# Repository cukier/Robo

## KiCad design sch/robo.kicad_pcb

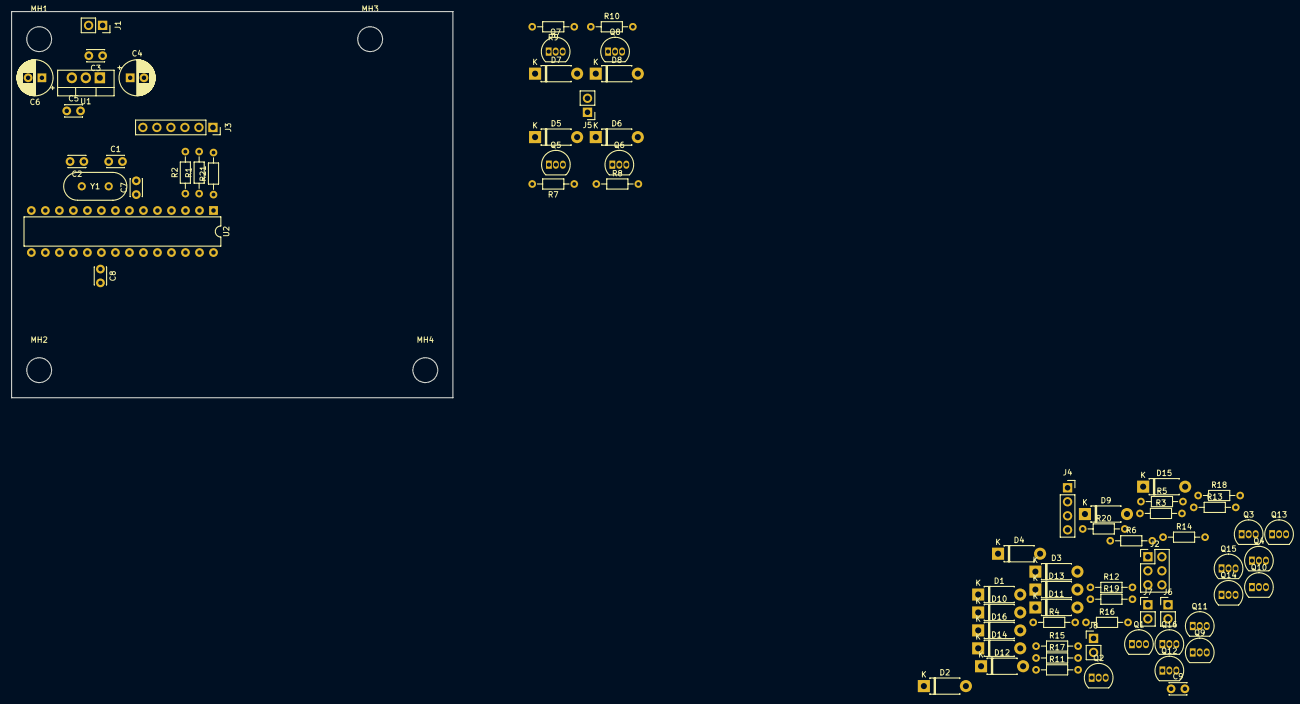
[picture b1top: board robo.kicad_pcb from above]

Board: 2 copper layers, 80.0 x 70.0 mm, 77 parts (0 on the bottom side), 47 nets, no tracks yet.

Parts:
C1, C2: 22nF; C_Disc_D3.0mm_W2.0mm_P2.50mm
C3, C5, C7, C8, C9: 100nF; C_Disc_D3.0mm_W2.0mm_P2.50mm
C4, C6: 470uF; CP_Radial_D6.3mm_P2.50mm
D1, D2, D3, D4, D5, D6, D7, D8, D9, D10, D11, D12, D13, D14, D15, D16: D; D_DO-41_SOD81_P7.62mm_Horizontal
J1: PWR; PinSocket_1x02_P2.54mm_Vertical
J2: ICSP; PinHeader_2x03_P2.54mm_Vertical
J3: Serial; PinSocket_1x06_P2.54mm_Vertical
J4: HC-04; PinSocket_1x04_P2.54mm_Vertical
J5: MOTOR 1; PinHeader_1x02_P2.54mm_Vertical
J6: MOTOR 4; PinHeader_1x02_P2.54mm_Vertical
J7: MOTOR 3; PinHeader_1x02_P2.54mm_Vertical
J8: MOTOR 2; PinHeader_1x02_P2.54mm_Vertical
MH1, MH2, MH3, MH4: MountingHole; MountingHole_4.5mm
Q1, Q2, Q3, Q4, Q5, Q6, Q7, Q8, Q9, Q10, Q11, Q12, Q13, Q14, Q15, Q16: BC337; TO-92_Inline
R1, R2, R3, R4, R5, R6, R7, R8, R9, R10, R11, R12, R13, R14, R15, R16, R17, R18, R19, R20, R21: 1k; R_Axial_DIN0204_L3.6mm_D1.6mm_P7.62mm_Horizontal
U1: L7805; TO-220-3_Vertical
U2: ATmega328P-PU; DIP-28_W7.62mm
Y1: Crystal; Crystal_HC49-4H_Vertical

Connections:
+5V: C5.1, C6.1, C7.1, C8.1, C9.1, D1.1, D3.1, D5.1, D7.1, D9.1, D11.1, D13.1, D15.1, J2.6, J4.1, Q1.1, Q3.1, Q5.1, Q7.1, Q9.1, Q11.1, Q13.1, Q15.1, R21.2, U1.3, U2.7, U2.20
/BRIDGE_H1: R7.2, R10.2, U2.4
/BRIDGE_H2: R17.2, R20.2, U2.5
/BRIDGE_H3: R3.2, R6.2, U2.6
/BRIDGE_H4: R13.2, R16.2, U2.11
/BRIDGE_L1: R8.2, R9.2, U2.23
/BRIDGE_L2: R18.2, R19.2, U2.24
/BRIDGE_L3: R4.2, R5.2, U2.25
/BRIDGE_L4: R14.2, R15.2, U2.26
/MISO: J2.1, U2.18
/MOSI: J2.5, U2.17
/MOTOR_H1: D5.2, D6.1, J5.1, J8.1, Q5.3, Q6.1
/MOTOR_H2: D9.2, D10.1, D13.2, D14.1, Q9.3, Q10.1, Q13.3, Q14.1
/MOTOR_H3: D1.2, D2.1, J6.1, Q1.3, Q2.1
/MOTOR_L1: D7.2, D8.1, J5.2, J8.2, Q7.3, Q8.1
/MOTOR_L2: D11.2, D12.1, D15.2, D16.1, Q11.3, Q12.1, Q15.3, Q16.1
/MOTOR_L3: D3.2, D4.1, J6.2, Q3.3, Q4.1
/RET: R12.2, U2.13
/RX: R1.1, U2.2
/SCK: J2.2, U2.19
/TRIG: R11.2, U2.12
/TX: R2.1, U2.3
/XTAL1: C1.1, U2.9, Y1.1
/XTAL2: C2.1, U2.10, Y1.2
/~RST: J2.3, R21.1, U2.1
GND: C1.2, C2.2, C3.2, C4.2, C5.2, C6.2, C7.2, C8.2, C9.2, D2.2, D4.2, D6.2, D8.2, D10.2, D12.2, D14.2, D16.2, J1.2, J2.4, J3.6, J4.4, Q2.3, Q4.3, Q6.3, Q8.3, Q10.3, Q12.3, Q14.3, Q16.3, U1.2, U2.8, U2.22
unnamed: C3.1, C4.1, J1.1, U1.1
unnamed: J3.2, R1.2
unnamed: J3.3, R2.2
unnamed: J4.2, R11.1
unnamed: J4.3, R12.1
unnamed: Q1.2, R3.1
unnamed: Q2.2, R4.1
unnamed: Q3.2, R5.1
unnamed: Q4.2, R6.1
unnamed: Q5.2, R7.1
unnamed: Q6.2, R8.1
unnamed: Q7.2, R9.1
unnamed: Q8.2, R10.1
unnamed: Q9.2, R13.1
unnamed: Q10.2, R14.1
unnamed: Q11.2, R15.1
unnamed: Q12.2, R16.1
unnamed: Q13.2, R17.1
unnamed: Q14.2, R18.1
unnamed: Q15.2, R19.1
unnamed: Q16.2, R20.1

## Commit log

2018-10-08 sch inicial
2018-10-09 posicionamento Signed-off-by: cukier <mauriciocukier@gmail.com>
